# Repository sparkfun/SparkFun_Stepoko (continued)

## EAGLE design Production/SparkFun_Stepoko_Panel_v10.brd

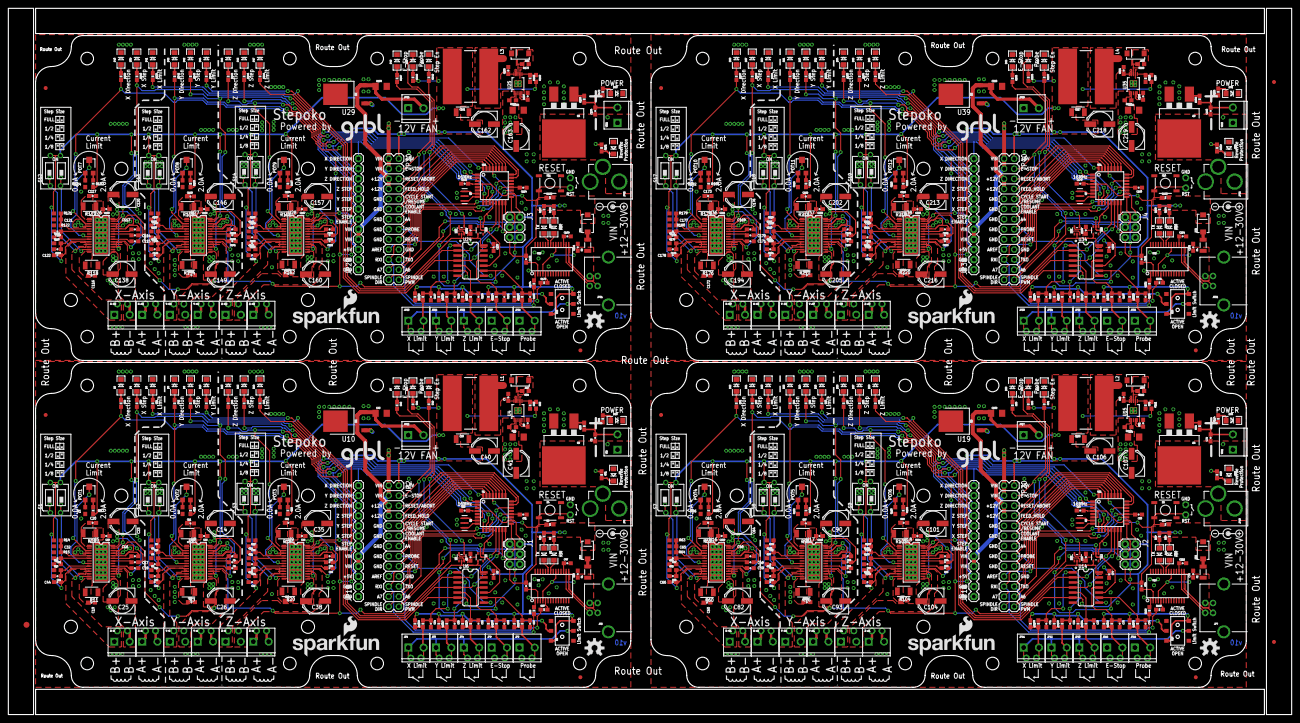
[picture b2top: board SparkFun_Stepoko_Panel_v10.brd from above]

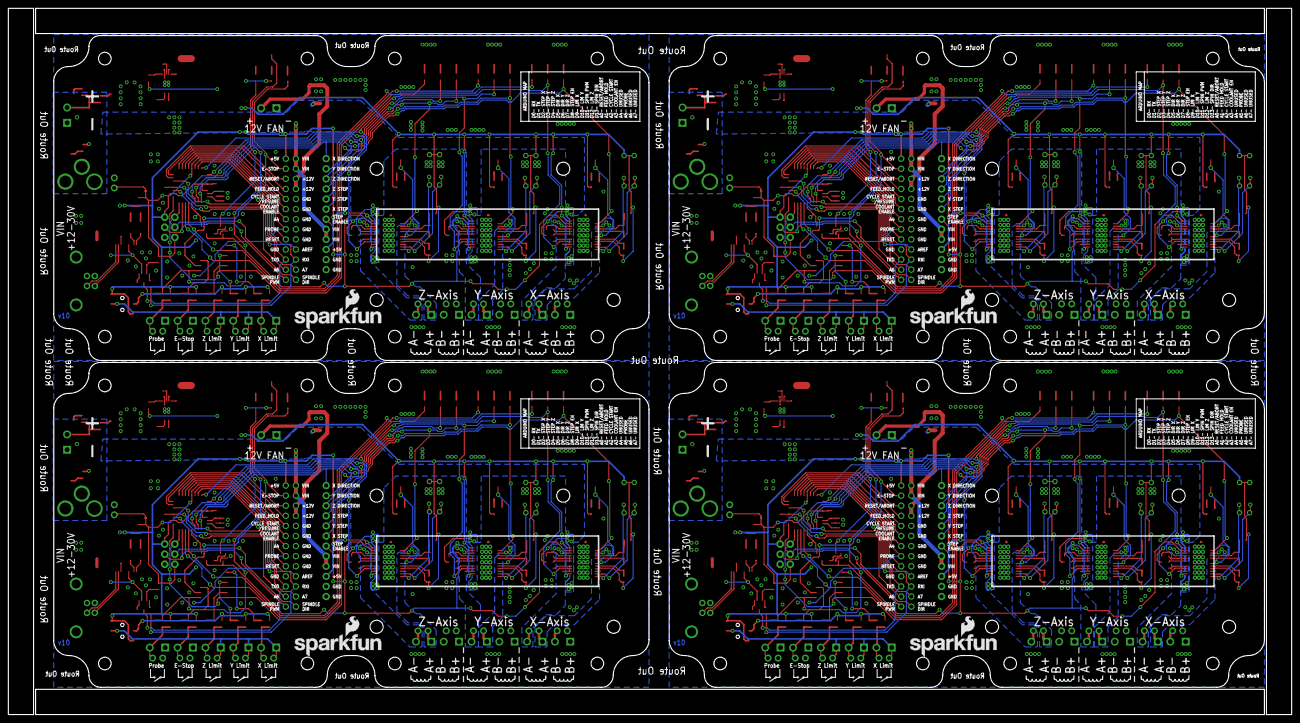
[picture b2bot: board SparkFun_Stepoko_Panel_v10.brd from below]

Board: 2 copper layers, 323.1 x 177.8 mm, 731 parts (4 on the bottom side), 532 nets.

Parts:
C1, C6, C8, C16, C17, C18, C27, C28, C29, C48, C49, C59, C83, C84, C85, C94, C95, C96, C113, C114, C115, C139, C140, C141, C150, C151, C152, C169, C170, C171, C195, C196, C197, C206, C207, C208: 0.22uF; 0603-CAP
C2, C3, C5, C7, C10, C11, C19, C20, C24, C30, C31, C37, C43, C44, C45, C46, C47, C50, C51, C52, C53, C54, C55, C56, C57, C58, C60, C61, C66, C67, C68, C69, C70, C71, C72, C73, C74, C75, C76, C77, C78, C80, C86, C87, C92, C97, C98, C103, C109, C110, C111, C112, C116, C117, C122, C123, C124, C125, C126, C127, C128, C129, C130, C131, C132, C133, C134, C136, C142, C143, C148, C153, C154, C159, C165, C166, C167, C168, C172, C173, C178, C179, C180, C181, C182, C183, C184, C185, C186, C187, C188, C189, C190, C192, C198, C199, C204, C209, C210, C215, C221, C222, C223, C224: 0.1uF; 0603-CAP
C4, C42, C79, C108, C135, C164, C191, C220: 1.0uF; 1206
C9, C81, C137, C193: 10nF; 0603-CAP
C12, C13, C21, C22, C33, C34, C62, C63, C88, C89, C99, C100, C118, C119, C144, C145, C155, C156, C174, C175, C200, C201, C211, C212: 1000pF; 0603-CAP
C14, C23, C25, C26, C35, C38, C40, C41, C64, C82, C90, C93, C101, C104, C106, C107, C120, C138, C146, C149, C157, C160, C162, C163, C176, C194, C202, C205, C213, C216, C218, C219: 47uF; PANASONIC_D
C15, C32, C36, C65, C91, C102, C121, C147, C158, C177, C203, C214: 0.18uF; 0603
C39, C105, C161, C217: 22uF; 1210
D1, D3, D5, D7, D9, D13, D19, D22, D25, D28, D30, D33, D37, D40, D43, D46, D48, D51, D55, D58, D61, D64, D66, D69: RED; LED-1206
D2, D4, D8, D12, D15, D20, D21, D24, D27, D32, D38, D39, D42, D45, D50, D56, D57, D60, D63, D68: GREEN; LED-1206
D6, D10, D14, D23, D26, D29, D41, D44, D47, D59, D62, D65: Yellow; LED-1206
D11, D18, D31, D35, D49, D53, D67, D71: BLUE; LED-1206
D16, D17, D34, D36, D52, D54, D70, D72: MBRA140; SMA-DIODE
E$1: FIDUCIAL-1.5X3
E$4, E$5: FIDUCIAL-1X2
F1, F2, F3, F4: PTCSMD; PTC-1206
FID1, FID2, FID3, FID4, FID5, FID6, FID7, FID8: FIDUCIAL1X2; FIDUCIAL-1X2
J1, J2, J3, J4: AVR ISP; 2X3
JP1, JP3, JP4, JP8, JP9, JP11, JP12, JP13, JP14, JP15, JP16, JP17, JP23, JP24, JP25, JP26, JP27, JP28, JP33, JP34, JP35, JP36, JP37, JP38: 3.5mm; SCREWTERMINAL-3.5MM-2_LOCK
JP2, JP20, JP30, JP40: 2X13
JP5, JP7, JP21, JP31: USB-B; USB-B-PTH
JP6, JP10, JP22, JP32: POWER; POWER_JACK_PTH_LOCK
JP18, JP19, JP29, JP39: 1X12
L1, L2, L3, L4: 27uH; INDUCTOR_SDR1307
LOGO1, LOGO4, LOGO7, LOGO10: OSHW-LOGOM; OSHW-LOGO-M
LOGO2, LOGO5, LOGO8, LOGO11: SFE_LOGO_NAME_FLAME.2_INCH; SFE_LOGO_NAME_FLAME_.2@1
LOGO3, LOGO6, LOGO9, LOGO12: SFE_LOGO_NAME_FLAME.2_INCH; SFE_LOGO_NAME_FLAME_.2
POT1, POT2, POT3, POT4, POT5, POT6, POT7, POT8, POT9, POT10, POT11, POT12: 2K_LINEAR_POT_SMD; TC33X
Q1, Q3, Q5, Q7: 16MHZ; RESONATOR-SMD
Q2, Q4, Q6, Q8: 100A/100V; TO-263/D2PAK
R1, R17, R26, R66, R102, R110, R124, R160, R168, R182, R218, R226: 0; 0603
R2, R3, R10, R11, R19, R20, R59, R60, R95, R96, R103, R104, R117, R118, R153, R154, R161, R162, R175, R176, R211, R212, R219, R220: 0.1; 1210
R4, R5, R12, R13, R21, R22, R61, R62, R97, R98, R105, R106, R119, R120, R155, R156, R163, R164, R177, R178, R213, R214, R221, R222: 39K; 0603
R6, R27, R28, R29, R35, R38, R51, R52, R56, R67, R70, R71, R72, R76, R78, R93, R94, R114, R125, R128, R129, R130, R134, R136, R151, R152, R172, R183, R186, R187, R188, R192, R194, R209, R210, R230: 10K; 0603-RES
R7, R8, R14, R15, R23, R24, R63, R64, R99, R100, R107, R108, R121, R122, R157, R158, R165, R166, R179, R180, R215, R216, R223, R224: 5.6K; 0603
R9, R18, R30, R31, R32, R33, R34, R36, R39, R40, R41, R42, R43, R44, R45, R46, R47, R48, R49, R50, R57, R58, R68, R69, R73, R74, R75, R77, R79, R80, R81, R82, R83, R84, R85, R86, R87, R88, R89, R90, R91, R92, R115, R116, R126, R127, R131, R132, R133, R135, R137, R138, R139, R140, R141, R142, R143, R144, R145, R146, R147, R148, R149, R150, R173, R174, R184, R185, R189, R190, R191, R193, R195, R196, R197, R198, R199, R200, R201, R202, R203, R204, R205, R206, R207, R208, R231, R232: 1K; 0603-RES
R16, R25, R37, R65, R101, R109, R123, R159, R167, R181, R217, R225: 3.3K; 0603-RES
R53, R111, R169, R227: 9.76K; 0603
R54, R112, R170, R228: 50.0m; 0603
R55, R113, R171, R229: 348K; 0603
S1, S2, S3, S7, S8, S9, S12, S13, S14, S17, S18, S19: 2-POS-DIPCTS-THRU-HOLE; 209-2LPST
S4, S6, S11, S16: Reset; TACTILE-SWITCH-SMD
S5, S10, S15, S20: DPDT; AYZ0202
U1, U11, U21, U31: ATMEGA328; TQFP32-08@1
U2, U12, U22, U32: FT232RLSSOP; SSOP28DB
U3, U20, U30, U40: 74LVC1G04; SOT353
U4, U15, U25, U35: LM25011; HVSS0P-10
U5, U8, U9, U16, U17, U18, U26, U27, U28, U36, U37, U38: DRV8811; HTSSOP28
U6, U14, U24, U34: 74HC7014D; SOIC-14
U7, U13, U23, U33: 7432SE; SOT353
U10, U19, U29, U39: +12v; TO-252
U$1, U$6, U$11, U$16: FLANGED_RED_ENCLOSURE-DIMENSION-NO-INNER-HOLES
U$2, U$3, U$4, U$5, U$7, U$8, U$9, U$10, U$12, U$13, U$14, U$15, U$17, U$18, U$19, U$20: STAND-OFF
VIN, VIN1, VIN2, VIN3: 3.5mm; SCREWTERMINAL-3.5MM-2_LOCK
X-A, X-A1, X-A2, X-A3: 3.5mm; SCREWTERMINAL-3.5MM-2_LOCK
X-B, X-B1, X-B2, X-B3: 3.5mm; SCREWTERMINAL-3.5MM-2_LOCK
Y-A, Y-A1, Y-A2, Y-A3: 3.5mm; SCREWTERMINAL-3.5MM-2_LOCK
Y-B, Y-B1, Y-B2, Y-B3: 3.5mm; SCREWTERMINAL-3.5MM-2_LOCK
Z-A, Z-A1, Z-A2, Z-A3: 3.5mm; SCREWTERMINAL-3.5MM-2_LOCK
Z-B, Z-B1, Z-B2, Z-B3: 3.5mm; SCREWTERMINAL-3.5MM-2_LOCK

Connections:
5V: C3.1, C5.1, C24.1, C37.1, C39.1, C40.+, C44.1, C50.2, D16.C, J1.2, JP2.2, JP19.3, L1.P$2, R6.2, R7.2, R9.2, R14.2, R16.2, R18.2, R23.2, R25.2, R29.1, R35.1, R37.2, R44.2, R53.2, S1.3, S1.4, S2.3, S2.4, S3.3, S3.4, S5.1, S5.6, U1.4, U1.6, U1.18, U3.5, U5.10, U5.17, U5.27, U6.14, U7.5, U8.10, U8.17, U8.27, U9.10, U9.17, U9.27
5V1: C66.1, C67.2, C76.1, C77.1, C92.1, C103.1, C105.1, C106.+, D36.C, J2.2, JP18.3, JP20.2, L2.P$2, R63.2, R65.2, R67.2, R68.2, R69.2, R72.1, R76.1, R90.2, R99.2, R101.2, R107.2, R109.2, R111.2, S7.3, S7.4, S8.3, S8.4, S9.3, S9.4, S10.1, S10.6, U11.4, U11.6, U11.18, U13.5, U14.14, U16.10, U16.17, U16.27, U17.10, U17.17, U17.27, U18.10, U18.17, U18.27, U20.5
5V2: C122.1, C123.2, C132.1, C133.1, C148.1, C159.1, C161.1, C162.+, D54.C, J3.2, JP29.3, JP30.2, L3.P$2, R121.2, R123.2, R125.2, R126.2, R127.2, R130.1, R134.1, R148.2, R157.2, R159.2, R165.2, R167.2, R169.2, S12.3, S12.4, S13.3, S13.4, S14.3, S14.4, S15.1, S15.6, U21.4, U21.6, U21.18, U23.5, U24.14, U26.10, U26.17, U26.27, U27.10, U27.17, U27.27, U28.10, U28.17, U28.27, U30.5
5V3: C178.1, C179.2, C188.1, C189.1, C204.1, C215.1, C217.1, C218.+, D72.C, J4.2, JP39.3, JP40.2, L4.P$2, R179.2, R181.2, R183.2, R184.2, R185.2, R188.1, R192.1, R206.2, R215.2, R217.2, R223.2, R225.2, R227.2, S17.3, S17.4, S18.3, S18.4, S19.3, S19.4, S20.1, S20.6, U31.4, U31.6, U31.18, U33.5, U34.14, U36.10, U36.17, U36.27, U37.10, U37.17, U37.27, U38.10, U38.17, U38.27, U40.5
A0-RESET/ABORT: JP2.6, U1.23
A0-RESET/ABORT1: JP20.6, U11.23
A0-RESET/ABORT2: JP30.6, U21.23
A0-RESET/ABORT3: JP40.6, U31.23
A1: JP20.14, U11.27
A1-FEED_HOLD: JP2.8, U1.24
A1-FEED_HOLD1: JP20.8, U11.24
A1-FEED_HOLD2: JP30.8, U21.24
A1-FEED_HOLD3: JP40.8, U31.24
A2: JP20.24, U11.19
A2-CYCLE_START/RESUME: JP2.10, U1.25
A2-CYCLE_START/RESUME1: JP20.10, U11.25
A2-CYCLE_START/RESUME2: JP30.10, U21.25
A2-CYCLE_START/RESUME3: JP40.10, U31.25
A3: JP20.23, U11.22
A3-COOLANT_ENABLE: JP2.12, U1.26
A3-COOLANT_ENABLE1: JP20.12, U11.26
A3-COOLANT_ENABLE2: JP30.12, U21.26
A3-COOLANT_ENABLE3: JP40.12, U31.26
A4: JP2.14, U1.27
A5: JP30.14, U21.27
A5-PROBE: JP2.16, U1.28, U6.8
A5-PROBE1: JP20.16, U11.28, U14.8
A5-PROBE2: JP30.16, U21.28, U24.8
A5-PROBE3: JP40.16, U31.28, U34.8
A6: JP2.24, U1.19
A7: JP2.23, U1.22
A8: JP30.24, U21.19
A9: JP30.23, U21.22
A10: JP40.14, U31.27
A11: JP40.24, U31.19
A12: JP40.23, U31.22
AREF: C51.2, JP2.19, U1.20
AREF1: C68.2, JP20.19, U11.20
AREF2: C124.2, JP30.19, U21.20
AREF3: C180.2, JP40.19, U31.20
D2-STEP-X: JP19.7, R39.2, U1.32, U5.19
D2-STEP-X1: JP18.7, R82.2, U11.32, U16.19
D2-STEP-X2: JP29.7, R140.2, U21.32, U26.19
D2-STEP-X3: JP39.7, R198.2, U31.32, U36.19
D3-STEP-Y: JP19.8, R43.2, U1.1, U8.19
D3-STEP-Y1: JP18.8, R85.2, U11.1, U17.19
D3-STEP-Y2: JP29.8, R143.2, U21.1, U27.19
D3-STEP-Y3: JP39.8, R201.2, U31.1, U37.19
D4-STEP-Z: JP19.9, R47.2, U1.2, U9.19
D4-STEP-Z1: JP18.9, R88.2, U11.2, U18.19
D4-STEP-Z2: JP29.9, R146.2, U21.2, U28.19
D4-STEP-Z3: JP39.9, R204.2, U31.2, U38.19
D5-DIR-X: JP19.12, R32.2, U1.9, U5.3
D5-DIR-X1: JP18.12, R81.2, U11.9, U16.3
D5-DIR-X2: JP29.12, R139.2, U21.9, U26.3
D5-DIR-X3: JP39.12, R197.2, U31.9, U36.3
D6-DIR-Y: JP19.11, R42.2, U1.10, U8.3
D6-DIR-Y1: JP18.11, R84.2, U11.10, U17.3
D6-DIR-Y2: JP29.11, R142.2, U21.10, U27.3
D6-DIR-Y3: JP39.11, R200.2, U31.10, U37.3
D7-DIR-Z: JP19.10, R46.2, U1.11, U9.3
D7-DIR-Z1: JP18.10, R87.2, U11.11, U18.3
D7-DIR-Z2: JP29.10, R145.2, U21.11, U28.3
D7-DIR-Z3: JP39.10, R203.2, U31.11, U38.3
D8-STEP_EN: U1.12, U7.1
D8-STEP_EN1: U11.12, U13.1
D8-STEP_EN2: U21.12, U23.1
D8-STEP_EN3: U31.12, U33.1
D9-LIM-X: R31.2, U1.13, U6.2
D9-LIM-X1: R80.2, U11.13, U14.2
D9-LIM-X2: R138.2, U21.13, U24.2
D9-LIM-X3: R196.2, U31.13, U34.2
D10-LIM-Y: R41.2, U1.14, U6.4
D10-LIM-Y1: R83.2, U11.14, U14.4
D10-LIM-Y2: R141.2, U21.14, U24.4
D10-LIM-Y3: R199.2, U31.14, U34.4
D+: JP5.D+, U2.15
D+1: JP7.D+, U12.15
D+2: JP21.D+, U22.15
D+3: JP31.D+, U32.15
D-: JP5.D-, U2.16
D-1: JP7.D-, U12.16
D-2: JP21.D-, U22.16
D-3: JP31.D-, U32.16
DTR: C52.2, U2.2
DTR1: C69.2, U12.2
DTR2: C125.2, U22.2
DTR3: C181.2, U32.2
ESTOP: C58.1, R48.2, U6.11
ESTOP1: C75.1, R79.2, U14.11
ESTOP2: C131.1, R137.2, U24.11
ESTOP3: C187.1, R195.2, U34.11
ESTOP-LOGIC: JP2.4, R40.2, U6.10, U7.2
ESTOP-LOGIC1: JP20.4, R89.2, U13.2, U14.10
ESTOP-LOGIC2: JP30.4, R147.2, U23.2, U24.10
ESTOP-LOGIC3: JP40.4, R205.2, U33.2, U34.10
GND: C3.2, C4.2, C5.2, C8.1, C9.2, C10.2, C11.2, C12.2, C13.2, C14.-, C15.2, C18.1, C19.2, C20.2, C21.2, C22.2, C23.-, C24.2, C25.-, C26.-, C29.1, C30.2, C31.2, C32.2, C33.2, C34.2, C35.-, C36.2, C37.2, C38.-, C39.2, C40.-, C41.-, C42.2, C43.2, C44.2, C45.2, C46.2, C47.2, C50.1, C51.1, C53.2, C54.2, C55.2, C56.2, C57.2, C58.2, D4.C, D5.C, D6.C, D7.C, D8.C, D9.C, D10.C, D12.C, D13.C, D14.C, D15.C, D18.C, J1.6, JP2.9, JP2.11, JP2.13, JP2.15, JP2.17, JP2.20, JP5.GND, JP8.1, JP9.1, JP15.1, JP19.1, JP19.2, Q1.2, Q2.3, R1.1, R2.1, R3.1, R4.1, R5.1, R8.1, R10.1, R11.1, R12.1, R13.1, R15.1, R17.1, R19.1, R20.1, R21.1, R22.1, R24.1, R26.1, R52.2, R54.1, S4.1, S5.3, S5.4, U1.3, U1.5, U1.21, U2.7, U2.18, U2.21, U2.25, U2.26, U3.3, U4.5, U4.7, U4.PAD, U5.7, U5.16, U5.21, U5.GND@10, U5.GND@11, U5.GND@12, U5.GND@13, U5.GND@14, U5.GND@15, U5.GND@16, U5.GND@17, U5.GND@18, U5.GND@19, U5.GND@20, U5.GND@21, U5.GND@22, U5.GND@23, U5.GND@24, U5.GND@25, U5.GND@26, U5.GND@27, U5.GND@28, U5.GND@29, U5.GND@30, U5.GND@PAD, U6.7, U6.13, U7.3, U8.7, U8.16, U8.21, U8.GND@10, U8.GND@11, U8.GND@12, U8.GND@13, U8.GND@14, U8.GND@15, U8.GND@16, U8.GND@17, U8.GND@18, U8.GND@19, U8.GND@20, U8.GND@21, U8.GND@22, U8.GND@23, U8.GND@24, U8.GND@25, U8.GND@26, U8.GND@27, U8.GND@28, U8.GND@29, U8.GND@30, U8.GND@PAD, U9.7, U9.16, U9.21, U9.GND@10, U9.GND@11, U9.GND@12, U9.GND@13, U9.GND@14, U9.GND@15, U9.GND@16, U9.GND@17, U9.GND@18, U9.GND@19, U9.GND@20, U9.GND@21, U9.GND@22, U9.GND@23, U9.GND@24, U9.GND@25, U9.GND@26, U9.GND@27, U9.GND@28, U9.GND@29, U9.GND@30, U9.GND@PAD, U10.3
GND1: C59.1, C60.2, C61.2, C62.2, C63.2, C64.-, C65.2, C66.2, C67.1, C68.1, C70.2, C71.2, C72.2, C73.2, C74.2, C75.2, C76.2, C77.2, C79.2, C81.2, C82.-, C85.1, C86.2, C87.2, C88.2, C89.2, C90.-, C91.2, C92.2, C93.-, C96.1, C97.2, C98.2, C99.2, C100.2, C101.-, C102.2, C103.2, C104.-, C105.2, C106.-, C107.-, C108.2, C109.2, C110.2, C111.2, C112.2, D21.C, D22.C, D23.C, D24.C, D25.C, D26.C, D27.C, D28.C, D29.C, D30.C, D32.C, D35.C, J2.6, JP7.GND, JP14.1, JP16.1, JP17.1, JP18.1, JP18.2, JP20.9, JP20.11, JP20.13, JP20.15, JP20.17, JP20.20, Q3.2, Q4.3, R59.1, R60.1, R61.1, R62.1, R64.1, R66.1, R94.2, R95.1, R96.1, R97.1, R98.1, R100.1, R102.1, R103.1, R104.1, R105.1, R106.1, R108.1, R110.1, R112.1, S6.1, S10.3, S10.4, U11.3, U11.5, U11.21, U12.7, U12.18, U12.21, U12.25, U12.26, U13.3, U14.7, U14.13, U15.5, U15.7, U15.PAD, U16.7, U16.16, U16.21, U16.GND@10, U16.GND@11, U16.GND@12, U16.GND@13, U16.GND@14, U16.GND@15, U16.GND@16, U16.GND@17, U16.GND@18, U16.GND@19, U16.GND@20, U16.GND@21, U16.GND@22, U16.GND@23, U16.GND@24, U16.GND@25, U16.GND@26, U16.GND@27, U16.GND@28, U16.GND@29, U16.GND@30, U16.GND@PAD, U17.7, U17.16, U17.21, U17.GND@10, U17.GND@11, U17.GND@12, U17.GND@13, U17.GND@14, U17.GND@15, U17.GND@16, U17.GND@17, U17.GND@18, U17.GND@19, U17.GND@20, U17.GND@21, U17.GND@22, U17.GND@23, U17.GND@24, U17.GND@25, U17.GND@26, U17.GND@27, U17.GND@28, U17.GND@29, U17.GND@30, U17.GND@PAD, U18.7, U18.16, U18.21, U18.GND@10, U18.GND@11, U18.GND@12, U18.GND@13, U18.GND@14, U18.GND@15, U18.GND@16, U18.GND@17, U18.GND@18, U18.GND@19, U18.GND@20, U18.GND@21, U18.GND@22, U18.GND@23, U18.GND@24, U18.GND@25, U18.GND@26, U18.GND@27, U18.GND@28, U18.GND@29, U18.GND@30, U18.GND@PAD, U19.3, U20.3
GND2: C115.1, C116.2, C117.2, C118.2, C119.2, C120.-, C121.2, C122.2, C123.1, C124.1, C126.2, C127.2, C128.2, C129.2, C130.2, C131.2, C132.2, C133.2, C135.2, C137.2, C138.-, C141.1, C142.2, C143.2, C144.2, C145.2, C146.-, C147.2, C148.2, C149.-, C152.1, C153.2, C154.2, C155.2, C156.2, C157.-, C158.2, C159.2, C160.-, C161.2, C162.-, C163.-, C164.2, C165.2, C166.2, C167.2, C168.2, D39.C, D40.C, D41.C, D42.C, D43.C, D44.C, D45.C, D46.C, D47.C, D48.C, D50.C, D53.C, J3.6, JP21.GND, JP26.1, JP27.1, JP28.1, JP29.1, JP29.2, JP30.9, JP30.11, JP30.13, JP30.15, JP30.17, JP30.20, Q5.2, Q6.3, R117.1, R118.1, R119.1, R120.1, R122.1, R124.1, R152.2, R153.1, R154.1, R155.1, R156.1, R158.1, R160.1, R161.1, R162.1, R163.1, R164.1, R166.1, R168.1, R170.1, S11.1, S15.3, S15.4, U21.3, U21.5, U21.21, U22.7, U22.18, U22.21, U22.25, U22.26, U23.3, U24.7, U24.13, U25.5, U25.7, U25.PAD, U26.7, U26.16, U26.21, U26.GND@10, U26.GND@11, U26.GND@12, U26.GND@13, U26.GND@14, U26.GND@15, U26.GND@16, U26.GND@17, U26.GND@18, U26.GND@19, U26.GND@20, U26.GND@21, U26.GND@22, U26.GND@23, U26.GND@24, U26.GND@25, U26.GND@26, U26.GND@27, U26.GND@28, U26.GND@29, U26.GND@30, U26.GND@PAD, U27.7, U27.16, U27.21, U27.GND@10, U27.GND@11, U27.GND@12, U27.GND@13, U27.GND@14, U27.GND@15, U27.GND@16, U27.GND@17, U27.GND@18, U27.GND@19, U27.GND@20, U27.GND@21, U27.GND@22, U27.GND@23, U27.GND@24, U27.GND@25, U27.GND@26, U27.GND@27, U27.GND@28, U27.GND@29, U27.GND@30, U27.GND@PAD, U28.7, U28.16, U28.21, U28.GND@10, U28.GND@11, U28.GND@12, U28.GND@13, U28.GND@14, U28.GND@15, U28.GND@16, U28.GND@17, U28.GND@18, U28.GND@19, U28.GND@20, U28.GND@21, U28.GND@22, U28.GND@23, U28.GND@24, U28.GND@25, U28.GND@26, U28.GND@27, U28.GND@28, U28.GND@29, U28.GND@30, U28.GND@PAD, U29.3, U30.3
GND3: C171.1, C172.2, C173.2, C174.2, C175.2, C176.-, C177.2, C178.2, C179.1, C180.1, C182.2, C183.2, C184.2, C185.2, C186.2, C187.2, C188.2, C189.2, C191.2, C193.2, C194.-, C197.1, C198.2, C199.2, C200.2, C201.2, C202.-, C203.2, C204.2, C205.-, C208.1, C209.2, C210.2, C211.2, C212.2, C213.-, C214.2, C215.2, C216.-, C217.2, C218.-, C219.-, C220.2, C221.2, C222.2, C223.2, C224.2, D57.C, D58.C, D59.C, D60.C, D61.C, D62.C, D63.C, D64.C, D65.C, D66.C, D68.C, D71.C, J4.6, JP31.GND, JP36.1, JP37.1, JP38.1, JP39.1, JP39.2, JP40.9, JP40.11, JP40.13, JP40.15, JP40.17, JP40.20, Q7.2, Q8.3, R175.1, R176.1, R177.1, R178.1, R180.1, R182.1, R210.2, R211.1, R212.1, R213.1, R214.1, R216.1, R218.1, R219.1, R220.1, R221.1, R222.1, R224.1, R226.1, R228.1, S16.1, S20.3, S20.4, U31.3, U31.5, U31.21, U32.7, U32.18, U32.21, U32.25, U32.26, U33.3, U34.7, U34.13, U35.5, U35.7, U35.PAD, U36.7, U36.16, U36.21, U36.GND@10, U36.GND@11, U36.GND@12, U36.GND@13, U36.GND@14, U36.GND@15, U36.GND@16, U36.GND@17, U36.GND@18, U36.GND@19, U36.GND@20, U36.GND@21, U36.GND@22, U36.GND@23, U36.GND@24, U36.GND@25, U36.GND@26, U36.GND@27, U36.GND@28, U36.GND@29, U36.GND@30, U36.GND@PAD, U37.7, U37.16, U37.21, U37.GND@10, U37.GND@11, U37.GND@12, U37.GND@13, U37.GND@14, U37.GND@15, U37.GND@16, U37.GND@17, U37.GND@18, U37.GND@19, U37.GND@20, U37.GND@21, U37.GND@22, U37.GND@23, U37.GND@24, U37.GND@25, U37.GND@26, U37.GND@27, U37.GND@28, U37.GND@29, U37.GND@30, U37.GND@PAD, U38.7, U38.16, U38.21, U38.GND@10, U38.GND@11, U38.GND@12, U38.GND@13, U38.GND@14, U38.GND@15, U38.GND@16, U38.GND@17, U38.GND@18, U38.GND@19, U38.GND@20, U38.GND@21, U38.GND@22, U38.GND@23, U38.GND@24, U38.GND@25, U38.GND@26, U38.GND@27, U38.GND@28, U38.GND@29, U38.GND@30, U38.GND@PAD, U39.3, U40.3
MISO-D12-LIMIT-Z: J1.1, R45.2, U1.16, U6.6
MISO-D12-LIMIT-Z1: J2.1, R86.2, U11.16, U14.6
MISO-D12-LIMIT-Z2: J3.1, R144.2, U21.16, U24.6
MISO-D12-LIMIT-Z3: J4.1, R202.2, U31.16, U34.6
MOSI-D11-SPINDLE_PWM: J1.4, JP2.26, U1.15
MOSI-D11-SPINDLE_PWM1: J2.4, JP20.26, U11.15
MOSI-D11-SPINDLE_PWM2: J3.4, JP30.26, U21.15
MOSI-D11-SPINDLE_PWM3: J4.4, JP40.26, U31.15
unnamed: R58.2, U2.1
unnamed: D2.A, R9.1
unnamed: D1.A, R18.1
unnamed: JP1.1, JP3.1, JP4.1, S5.5
unnamed: D7.A, R40.1
unnamed: Q1.3, U1.8
unnamed: JP1.2, R30.1, R38.2
unnamed: Q1.1, U1.7
unnamed: POT1.3, R37.1
unnamed: POT1.1, R1.2
unnamed: C12.1, R4.2, U8.6
unnamed: C13.1, R5.2, U8.9
unnamed: D11.A, R44.1
unnamed: C15.1, R7.1, R8.2, U8.5
unnamed: S2.2, U8.13
unnamed: D15.A, R49.1
unnamed: C2.1, D3.A, JP6.GND, Q2.2, VIN.1
unnamed: D6.A, R31.1
unnamed: D5.A, R32.1
unnamed: D4.A, R39.1
unnamed: R52.1, R53.1, U4.6
unnamed: D10.A, R41.1
unnamed: S2.1, U8.12
unnamed: C16.1, U5.24
unnamed: C16.2, U5.23
unnamed: C8.2, U8.20
unnamed: POT2.2, U8.8
unnamed: C21.1, R12.2, U5.6
unnamed: C22.1, R13.2, U5.9
unnamed: C32.1, R14.1, R15.2, U5.5
unnamed: D9.A, R42.1
unnamed: D1.C, U2.23
unnamed: D2.C, U2.22
unnamed: S1.2, U5.13
unnamed: S1.1, U5.12
unnamed: D8.A, R43.1
unnamed: U5.11, X-B.1
unnamed: C18.2, U5.20
unnamed: Q2.1, R50.2
unnamed: D14.A, R45.1
unnamed: D3.C, R51.2
unnamed: JP3.2, R27.2, R33.1
unnamed: JP4.2, R28.2, R34.1
unnamed: C62.1, R61.2, U16.6
unnamed: POT2.3, R16.1
unnamed: POT2.1, R17.2
unnamed: C6.2, U8.22
unnamed: C1.1, U8.24
unnamed: C1.2, U8.23
unnamed: U8.11, Y-B.1
unnamed: D16.A, F1.2
unnamed: C63.1, R62.2, U16.9
unnamed: JP8.2, R29.2, R36.1
unnamed: U8.18, Y-B.2
unnamed: U8.4, Y-A.1
unnamed: JP9.2, R35.2, R48.1
unnamed: U8.25, Y-A.2
unnamed: C10.1, R3.2, U8.14
unnamed: D18.A, R56.2
unnamed: D13.A, R46.1
unnamed: D12.A, R47.1
unnamed: R57.2, U2.5
unnamed: R55.1, U4.2
unnamed: C17.2, U5.22
unnamed: C7.1, U4.10
unnamed: U5.18, X-B.2
unnamed: C7.2, D17.C, L1.P$1, U4.9
unnamed: U5.4, X-A.1
unnamed: C11.1, R2.2, U8.1
unnamed: C33.1, R21.2, U9.6
unnamed: C34.1, R22.2, U9.9
unnamed: C36.1, R23.1, R24.2, U9.5
unnamed: S3.2, U9.13
unnamed: S3.1, U9.12
unnamed: C9.1, U4.4
unnamed: U5.25, X-A.2
unnamed: C29.2, U9.20
unnamed: POT3.2, U9.8
unnamed: POT3.3, R25.1
unnamed: POT3.1, R26.2
unnamed: C28.2, U9.22
unnamed: C27.1, U9.24
unnamed: C27.2, U9.23
unnamed: U9.11, Z-B.1
unnamed: U9.18, Z-B.2
unnamed: U9.4, Z-A.1
unnamed: U9.25, Z-A.2
unnamed: C30.1, R20.2, U9.14
unnamed: C19.1, R11.2, U5.14
unnamed: C31.1, R19.2, U9.1
unnamed: POT1.2, U5.8
unnamed: R27.1, R28.1, R38.1, S5.2
unnamed: C20.1, R10.2, U5.1
unnamed: D17.A, R54.2, U4.8
unnamed: C47.1, U2.17
unnamed: C65.1, R63.1, R64.2, U16.5
unnamed: S7.2, U16.13
unnamed: S7.1, U16.12
unnamed: C59.2, U16.20
unnamed: POT4.2, U16.8
unnamed: POT4.3, R65.1
unnamed: POT4.1, R66.2
unnamed: Q3.3, U11.8
unnamed: Q3.1, U11.7
unnamed: D19.C, U12.23
unnamed: D20.C, U12.22
unnamed: D20.A, R68.1
unnamed: D19.A, R69.1
unnamed: JP11.2, R73.1, R78.2
unnamed: JP12.2, R70.2, R74.1
unnamed: JP13.2, R71.2, R75.1
unnamed: JP14.2, R72.2, R77.1
unnamed: JP16.2, R76.2, R79.1
unnamed: D23.A, R80.1
unnamed: D22.A, R81.1
unnamed: D21.A, R82.1
unnamed: D26.A, R83.1
unnamed: D25.A, R84.1
unnamed: D24.A, R85.1
unnamed: D29.A, R86.1
unnamed: D28.A, R87.1
unnamed: D27.A, R88.1
unnamed: D30.A, R89.1
unnamed: D31.A, R90.1
unnamed: D32.A, R91.1
unnamed: C78.1, D33.A, JP10.GND, Q4.2, VIN1.1
unnamed: Q4.1, R92.2
unnamed: D33.C, R93.2
unnamed: C80.1, U15.10
unnamed: C80.2, D34.C, L2.P$1, U15.9
unnamed: C81.1, U15.4
unnamed: R94.1, R111.1, U15.6
unnamed: C49.2, U16.22
unnamed: C48.1, U16.24
unnamed: C48.2, U16.23
unnamed: U16.11, X-B1.1
unnamed: U16.18, X-B1.2
unnamed: U16.4, X-A1.1
unnamed: U16.25, X-A1.2
unnamed: C60.1, R60.2, U16.14
unnamed: C61.1, R59.2, U16.1
unnamed: C88.1, R97.2, U17.6
unnamed: C89.1, R98.2, U17.9
unnamed: C91.1, R99.1, R100.2, U17.5
unnamed: S8.2, U17.13
unnamed: S8.1, U17.12
unnamed: C85.2, U17.20
unnamed: POT5.2, U17.8
unnamed: POT5.3, R101.1
unnamed: POT5.1, R102.2
unnamed: C84.2, U17.22
unnamed: C83.1, U17.24
unnamed: C83.2, U17.23
unnamed: U17.11, Y-B1.1
unnamed: U17.18, Y-B1.2
unnamed: U17.4, Y-A1.1
unnamed: U17.25, Y-A1.2
unnamed: C86.1, R96.2, U17.14
unnamed: C87.1, R95.2, U17.1
unnamed: C99.1, R105.2, U18.6
unnamed: C100.1, R106.2, U18.9
unnamed: C102.1, R107.1, R108.2, U18.5
unnamed: S9.2, U18.13
unnamed: S9.1, U18.12
unnamed: C96.2, U18.20
unnamed: POT6.2, U18.8
unnamed: POT6.3, R109.1
unnamed: POT6.1, R110.2
unnamed: C95.2, U18.22
unnamed: C94.1, U18.24
unnamed: C94.2, U18.23
unnamed: U18.11, Z-B1.1
unnamed: U18.18, Z-B1.2
unnamed: U18.4, Z-A1.1
unnamed: U18.25, Z-A1.2
unnamed: C97.1, R104.2, U18.14
unnamed: C98.1, R103.2, U18.1
unnamed: R113.1, U15.2
unnamed: D35.A, R114.2
unnamed: D36.A, F2.2
unnamed: R70.1, R71.1, R78.1, S10.2
unnamed: JP11.1, JP12.1, JP13.1, S10.5
unnamed: D34.A, R112.2, U15.8
unnamed: R116.2, U12.1
unnamed: R115.2, U12.5
unnamed: C112.1, U12.17
unnamed: C118.1, R119.2, U26.6
unnamed: C119.1, R120.2, U26.9
unnamed: C121.1, R121.1, R122.2, U26.5
unnamed: S12.2, U26.13
unnamed: S12.1, U26.12
unnamed: C115.2, U26.20
unnamed: POT7.2, U26.8
unnamed: POT7.3, R123.1
unnamed: POT7.1, R124.2
unnamed: Q5.3, U21.8
unnamed: Q5.1, U21.7
unnamed: D37.C, U22.23
unnamed: D38.C, U22.22
unnamed: D38.A, R126.1
unnamed: D37.A, R127.1
unnamed: JP23.2, R131.1, R136.2
unnamed: JP24.2, R128.2, R132.1
unnamed: JP25.2, R129.2, R133.1
unnamed: JP26.2, R130.2, R135.1
unnamed: JP27.2, R134.2, R137.1
unnamed: D41.A, R138.1
unnamed: D40.A, R139.1
unnamed: D39.A, R140.1
unnamed: D44.A, R141.1
unnamed: D43.A, R142.1
unnamed: D42.A, R143.1
unnamed: D47.A, R144.1
unnamed: D46.A, R145.1
unnamed: D45.A, R146.1
unnamed: D48.A, R147.1
unnamed: D49.A, R148.1
unnamed: D50.A, R149.1
unnamed: C134.1, D51.A, JP22.GND, Q6.2, VIN2.1
unnamed: Q6.1, R150.2
unnamed: D51.C, R151.2
unnamed: C136.1, U25.10
unnamed: C136.2, D52.C, L3.P$1, U25.9
unnamed: C137.1, U25.4
unnamed: R152.1, R169.1, U25.6
unnamed: C114.2, U26.22
unnamed: C113.1, U26.24
unnamed: C113.2, U26.23
unnamed: U26.11, X-B2.1
unnamed: U26.18, X-B2.2
unnamed: U26.4, X-A2.1
unnamed: U26.25, X-A2.2
unnamed: C116.1, R118.2, U26.14
unnamed: C117.1, R117.2, U26.1
unnamed: C144.1, R155.2, U27.6
unnamed: C145.1, R156.2, U27.9
unnamed: C147.1, R157.1, R158.2, U27.5
unnamed: S13.2, U27.13
unnamed: S13.1, U27.12
unnamed: C141.2, U27.20
unnamed: POT8.2, U27.8
unnamed: POT8.3, R159.1
unnamed: POT8.1, R160.2
unnamed: C140.2, U27.22
unnamed: C139.1, U27.24
unnamed: C139.2, U27.23
unnamed: U27.11, Y-B2.1
unnamed: U27.18, Y-B2.2
unnamed: U27.4, Y-A2.1
unnamed: U27.25, Y-A2.2
unnamed: C142.1, R154.2, U27.14
unnamed: C143.1, R153.2, U27.1
unnamed: C155.1, R163.2, U28.6
unnamed: C156.1, R164.2, U28.9
unnamed: C158.1, R165.1, R166.2, U28.5
unnamed: S14.2, U28.13
unnamed: S14.1, U28.12
unnamed: C152.2, U28.20
unnamed: POT9.2, U28.8
unnamed: POT9.3, R167.1
unnamed: POT9.1, R168.2
unnamed: C151.2, U28.22
unnamed: C150.1, U28.24
unnamed: C150.2, U28.23
unnamed: U28.11, Z-B2.1
unnamed: U28.18, Z-B2.2
unnamed: U28.4, Z-A2.1
unnamed: U28.25, Z-A2.2
unnamed: C153.1, R162.2, U28.14
unnamed: C154.1, R161.2, U28.1
unnamed: R171.1, U25.2
unnamed: D53.A, R172.2
unnamed: D54.A, F3.2
unnamed: R128.1, R129.1, R136.1, S15.2
unnamed: JP23.1, JP24.1, JP25.1, S15.5
unnamed: D52.A, R170.2, U25.8
unnamed: R174.2, U22.1
unnamed: R173.2, U22.5
unnamed: C168.1, U22.17
unnamed: C174.1, R177.2, U36.6
unnamed: C175.1, R178.2, U36.9
unnamed: C177.1, R179.1, R180.2, U36.5
unnamed: S17.2, U36.13
unnamed: S17.1, U36.12
unnamed: C171.2, U36.20
unnamed: POT10.2, U36.8
unnamed: POT10.3, R181.1
unnamed: POT10.1, R182.2
unnamed: Q7.3, U31.8
unnamed: Q7.1, U31.7
unnamed: D55.C, U32.23
unnamed: D56.C, U32.22
unnamed: D56.A, R184.1
unnamed: D55.A, R185.1
unnamed: JP33.2, R189.1, R194.2
unnamed: JP34.2, R186.2, R190.1
unnamed: JP35.2, R187.2, R191.1
unnamed: JP36.2, R188.2, R193.1
unnamed: JP37.2, R192.2, R195.1
unnamed: D59.A, R196.1
unnamed: D58.A, R197.1
unnamed: D57.A, R198.1
unnamed: D62.A, R199.1
unnamed: D61.A, R200.1
unnamed: D60.A, R201.1
unnamed: D65.A, R202.1
unnamed: D64.A, R203.1
unnamed: D63.A, R204.1
unnamed: D66.A, R205.1
unnamed: D67.A, R206.1
unnamed: D68.A, R207.1
unnamed: C190.1, D69.A, JP32.GND, Q8.2, VIN3.1
unnamed: Q8.1, R208.2
unnamed: D69.C, R209.2
unnamed: C192.1, U35.10
unnamed: C192.2, D70.C, L4.P$1, U35.9
unnamed: C193.1, U35.4
unnamed: R210.1, R227.1, U35.6
unnamed: C170.2, U36.22
unnamed: C169.1, U36.24
unnamed: C169.2, U36.23
unnamed: U36.11, X-B3.1
unnamed: U36.18, X-B3.2
unnamed: U36.4, X-A3.1
unnamed: U36.25, X-A3.2
unnamed: C172.1, R176.2, U36.14
unnamed: C173.1, R175.2, U36.1
unnamed: C200.1, R213.2, U37.6
unnamed: C201.1, R214.2, U37.9
unnamed: C203.1, R215.1, R216.2, U37.5
unnamed: S18.2, U37.13
unnamed: S18.1, U37.12
unnamed: C197.2, U37.20
unnamed: POT11.2, U37.8
unnamed: POT11.3, R217.1
unnamed: POT11.1, R218.2
unnamed: C196.2, U37.22
unnamed: C195.1, U37.24
unnamed: C195.2, U37.23
unnamed: U37.11, Y-B3.1
unnamed: U37.18, Y-B3.2
unnamed: U37.4, Y-A3.1
unnamed: U37.25, Y-A3.2
unnamed: C198.1, R212.2, U37.14
unnamed: C199.1, R211.2, U37.1
unnamed: C211.1, R221.2, U38.6
unnamed: C212.1, R222.2, U38.9
unnamed: C214.1, R223.1, R224.2, U38.5
unnamed: S19.2, U38.13
unnamed: S19.1, U38.12
unnamed: C208.2, U38.20
unnamed: POT12.2, U38.8
unnamed: POT12.3, R225.1
unnamed: POT12.1, R226.2
unnamed: C207.2, U38.22
unnamed: C206.1, U38.24
unnamed: C206.2, U38.23
unnamed: U38.11, Z-B3.1
unnamed: U38.18, Z-B3.2
unnamed: U38.4, Z-A3.1
unnamed: U38.25, Z-A3.2
unnamed: C209.1, R220.2, U38.14
unnamed: C210.1, R219.2, U38.1
unnamed: R229.1, U35.2
unnamed: D71.A, R230.2
unnamed: D72.A, F4.2
unnamed: R186.1, R187.1, R194.1, S20.2
unnamed: JP33.1, JP34.1, JP35.1, S20.5
unnamed: D70.A, R228.2, U35.8
unnamed: R232.2, U32.1
unnamed: R231.2, U32.5
unnamed: C224.1, U32.17
PROBE: C57.1, D11.C, R36.2, U6.9
PROBE1: C74.1, D31.C, R77.2, U14.9
PROBE2: C130.1, D49.C, R135.2, U24.9
PROBE3: C186.1, D67.C, R193.2, U34.9
RESET: C52.1, J1.5, JP2.18, R6.1, S4.3, U1.29
RESET1: C69.1, J2.5, JP20.18, R67.1, S6.3, U11.29
RESET2: C125.1, J3.5, JP30.18, R125.1, S11.3, U21.29
RESET3: C181.1, J4.5, JP40.18, R183.1, S16.3, U31.29
RXI: JP2.21, R58.1, U1.30
RXI1: JP20.21, R116.1, U11.30
RXI2: JP30.21, R174.1, U21.30
RXI3: JP40.21, R232.1, U31.30
SCK-D13-SPINDLE_DIR: J1.3, JP2.25, U1.17
SCK-D13-SPINDLE_DIR1: J2.3, JP20.25, U11.17
SCK-D13-SPINDLE_DIR2: J3.3, JP30.25, U21.17
SCK-D13-SPINDLE_DIR3: J4.3, JP40.25, U31.17
STEP-EN_LED: R49.2, U3.4
STEP-EN_LED1: R91.2, U20.4
STEP-EN_LED2: R149.2, U30.4
STEP-EN_LED3: R207.2, U40.4
STEP_ENABLE: JP19.6, U3.2, U5.26, U7.4, U8.26, U9.26
STEP_ENABLE1: JP18.6, U13.4, U16.26, U17.26, U18.26, U20.2
STEP_ENABLE2: JP29.6, U23.4, U26.26, U27.26, U28.26, U30.2
STEP_ENABLE3: JP39.6, U33.4, U36.26, U37.26, U38.26, U40.2
TXO: JP2.22, R57.1, U1.31
TXO1: JP20.22, R115.1, U11.31
TXO2: JP30.22, R173.1, U21.31
TXO3: JP40.22, R231.1, U31.31
VCC: C42.1, JP2.5, JP2.7, JP15.2, U10.2
VCC1: C108.1, JP17.2, JP20.5, JP20.7, U19.2
VCC2: C164.1, JP28.2, JP30.5, JP30.7, U29.2
VCC3: C220.1, JP38.2, JP40.5, JP40.7, U39.2
VCC_USB: C53.1, F1.1, JP5.VBUS, U2.4, U2.20
VCC_USB1: C70.1, F2.1, JP7.VBUS, U12.4, U12.20
VCC_USB2: C126.1, F3.1, JP21.VBUS, U22.4, U22.20
VCC_USB3: C182.1, F4.1, JP31.VBUS, U32.4, U32.20
VIN: C2.2, C4.1, C6.1, C14.+, C17.1, C23.+, C25.+, C26.+, C28.1, C35.+, C38.+, C41.+, C43.1, C45.1, C46.1, JP2.1, JP2.3, JP6.PWR, JP19.4, JP19.5, R50.1, R51.1, R55.2, R56.1, U4.1, U5.15, U5.28, U8.15, U8.28, U9.15, U9.28, U10.1, VIN.2
VIN1: C49.1, C64.+, C78.2, C79.1, C82.+, C84.1, C90.+, C93.+, C95.1, C101.+, C104.+, C107.+, C109.1, C110.1, C111.1, JP10.PWR, JP18.4, JP18.5, JP20.1, JP20.3, R92.1, R93.1, R113.2, R114.1, U15.1, U16.15, U16.28, U17.15, U17.28, U18.15, U18.28, U19.1, VIN1.2
VIN2: C114.1, C120.+, C134.2, C135.1, C138.+, C140.1, C146.+, C149.+, C151.1, C157.+, C160.+, C163.+, C165.1, C166.1, C167.1, JP22.PWR, JP29.4, JP29.5, JP30.1, JP30.3, R150.1, R151.1, R171.2, R172.1, U25.1, U26.15, U26.28, U27.15, U27.28, U28.15, U28.28, U29.1, VIN2.2
VIN3: C170.1, C176.+, C190.2, C191.1, C194.+, C196.1, C202.+, C205.+, C207.1, C213.+, C216.+, C219.+, C221.1, C222.1, C223.1, JP32.PWR, JP39.4, JP39.5, JP40.1, JP40.3, R208.1, R209.1, R229.2, R230.1, U35.1, U36.15, U36.28, U37.15, U37.28, U38.15, U38.28, U39.1, VIN3.2
X_LIM: C54.1, R30.2, U6.1
X_LIM1: C71.1, R73.2, U14.1
X_LIM2: C127.1, R131.2, U24.1
X_LIM3: C183.1, R189.2, U34.1
Y_LIM: C55.1, R33.2, U6.3
Y_LIM1: C72.1, R74.2, U14.3
Y_LIM2: C128.1, R132.2, U24.3
Y_LIM3: C184.1, R190.2, U34.3
Z_LIM: C56.1, R34.2, U6.5
Z_LIM1: C73.1, R75.2, U14.5
Z_LIM2: C129.1, R133.2, U24.5
Z_LIM3: C185.1, R191.2, U34.5

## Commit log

2015-02-05 initial commit for v2 of GRBL Board
2015-02-05 schematic cleanup
2015-02-06 cleanup
2015-02-06 more cleanup
2015-02-06 renamed board and continued cleanup
2015-02-08 revision changes from review
2015-02-08 made changes from design review
2015-02-08 added prod-ids
2015-02-08 name change
2015-02-09 fixed all issued in github
2015-02-09 changes made from github
2015-03-02 making changes for second proto round
2015-03-03 finished modifications from proto review
2015-03-04 made changes and added logos. Added test points
2015-03-04 removed script
2015-03-04 made changes from issues in repo
2015-04-27 fixing high impedance issues
2015-04-28 enlarged stepper traces and improved Ground Planes
2015-04-28 moving components for ground pours
2015-04-29 more work on power planes
2015-05-01 Testing Assembly Variants
2015-05-04 adding room for heatsinks
2015-05-11 updated version numbers
2015-05-13 fixed designed by placement
2015-05-14 found via hitting trace
2015-05-14 corrected issues in github
2015-06-29 Corrected Probe functionality and updated silk to better reflect limit switch functionality, moved Arduino table to better fit board layout
2015-07-01 corrected issued from Design review. Opened up holes to prevent potential shorts, schematic cleanup.
2015-07-01 updated version number
2015-07-01 fixed current limit resistor values
2015-07-07 added test points to current limit resistors
2015-07-07 moved dimensions to fit with .01 grid
2015-07-07 created panel v10
2015-09-08 added heatsink design files
2015-09-27 added g-code
2015-09-27 Ready for fab
2015-10-01 moving along on testing
2015-10-01 updated current drive setting resistors
2015-10-01 saved temp log
2015-10-01 added readme and updated to v11 hardware
2015-11-02 added part docu
2015-11-10 Added notes folder
2015-11-10 Replaced 25v cap with 100v cap
2015-11-16 re-arranged example folders
2015-11-16 updated readme to reflect repo
2015-11-20 Added SF flame coaster gcodes
2015-11-20 Finalized documentation
2016-01-07 added kit parts checklist
2016-04-21 updated documentation
